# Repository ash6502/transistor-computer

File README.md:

# transistor-computer
wip transistor based computer

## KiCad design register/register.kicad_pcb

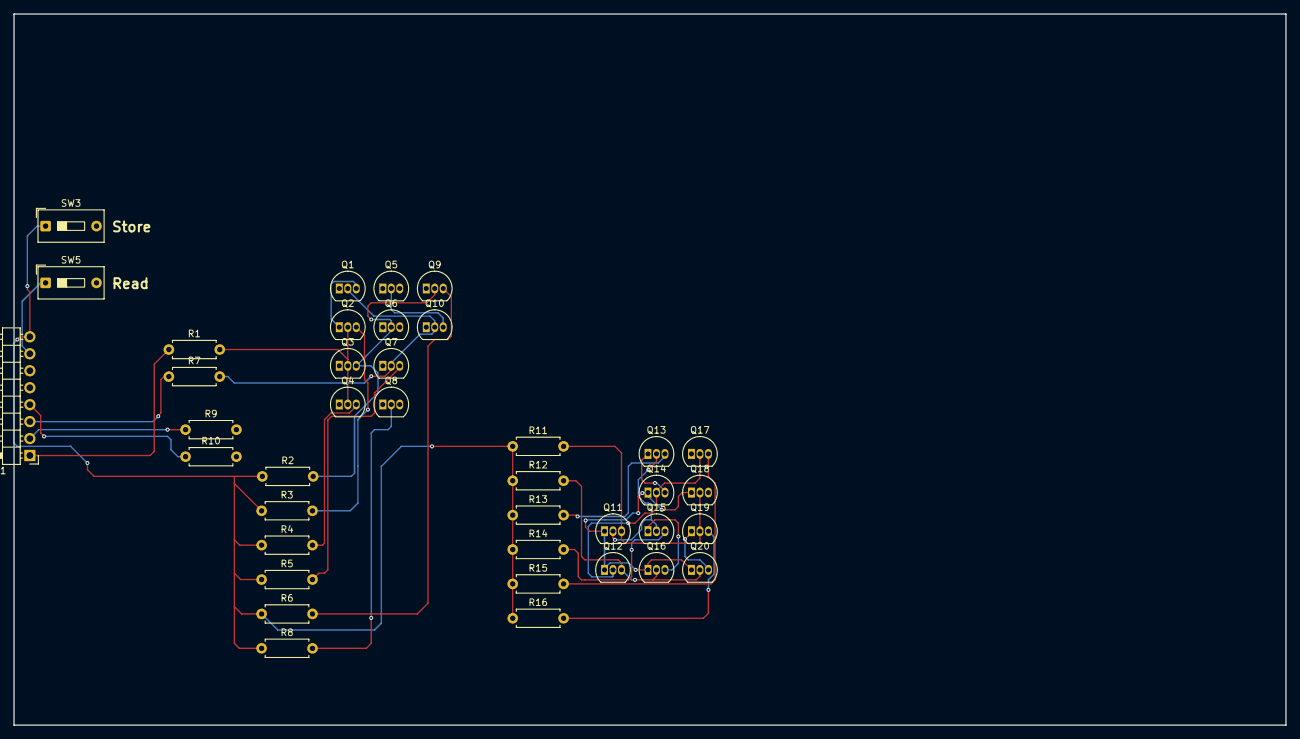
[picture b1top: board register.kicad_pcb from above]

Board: 2 copper layers, 190.5 x 106.5 mm, 39 parts (0 on the bottom side), 32 nets.

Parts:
J1: Conn_01x08; PinHeader_1x08_P2.54mm_Horizontal
Q1, Q2, Q3, Q4, Q5, Q6, Q7, Q8, Q9, Q10, Q11, Q12, Q13, Q14, Q15, Q16, Q17, Q18, Q19, Q20: PN2222A; TO-92_Inline
R1, R7, R9, R10: 1k; R_Axial_DIN0207_L6.3mm_D2.5mm_P7.62mm_Horizontal
R2, R3, R4, R5, R6, R8, R11, R12, R13, R14, R15, R16: 100; R_Axial_DIN0207_L6.3mm_D2.5mm_P7.62mm_Horizontal
SW3, SW5: SW_DIP_x01; SW_DIP_SPSTx01_Slide_9.78x4.72mm_W7.62mm_P2.54mm

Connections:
+5V: J1.8, R2.1, R3.1, R4.1, R5.1, R6.1, R8.1, R11.1, R12.1, R13.1, R14.1, R15.1, R16.1, SW3.1
/ColA: J1.3, R7.1
/ColB: J1.4, R10.1
/Read: J1.6, SW5.2
/RowA: J1.1, R1.1
/RowB: J1.2, R9.1
/Store: J1.5, SW3.2
GND: J1.7, Q1.1 (E), Q3.1 (E), Q5.1 (E), Q6.1 (E), Q8.1 (E), Q10.1 (E), Q11.1 (E), Q12.1 (E), Q14.1 (E), Q16.1 (E), Q18.1 (E), Q20.1 (E), SW5.1
unnamed: Q1.2 (B), Q7.2 (B), Q10.2 (B), R7.2
unnamed: Q1.3 (C), Q2.1 (E)
unnamed: Q2.2 (B), Q3.2 (B), Q4.2 (B), R1.2
unnamed: Q2.3 (C), R3.2
unnamed: Q3.3 (C), Q6.2 (B), Q9.2 (B), R2.2
unnamed: Q4.3 (C), R4.2
unnamed: Q4.1 (E), Q5.3 (C)
unnamed: Q6.3 (C), Q7.1 (E)
unnamed: Q7.3 (C), R5.2
unnamed: Q8.3 (C), Q9.1 (E)
unnamed: Q9.3 (C), R6.2
unnamed: Q5.2 (B), Q8.2 (B), Q10.3 (C), R8.2
unnamed: Q11.2 (B), Q13.2 (B), Q15.2 (B), R9.2
unnamed: Q11.3 (C), Q18.2 (B), Q19.2 (B), R11.2
unnamed: Q12.2 (B), Q14.2 (B), Q17.2 (B), R10.2
unnamed: Q12.3 (C), Q16.2 (B), Q20.2 (B), R12.2
unnamed: Q13.3 (C), R13.2
unnamed: Q13.1 (E), Q14.3 (C)
unnamed: Q15.3 (C), R14.2
unnamed: Q15.1 (E), Q16.3 (C)
unnamed: Q17.3 (C), R15.2
unnamed: Q17.1 (E), Q18.3 (C)
unnamed: Q19.3 (C), R16.2
unnamed: Q19.1 (E), Q20.3 (C)

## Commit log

2026-05-23 Added pins.drawio
